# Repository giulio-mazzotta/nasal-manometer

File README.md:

# nasal-manometer

This repository contains the circuit design and the software to measure the nasal pressure while speaking using a nasal cannula.

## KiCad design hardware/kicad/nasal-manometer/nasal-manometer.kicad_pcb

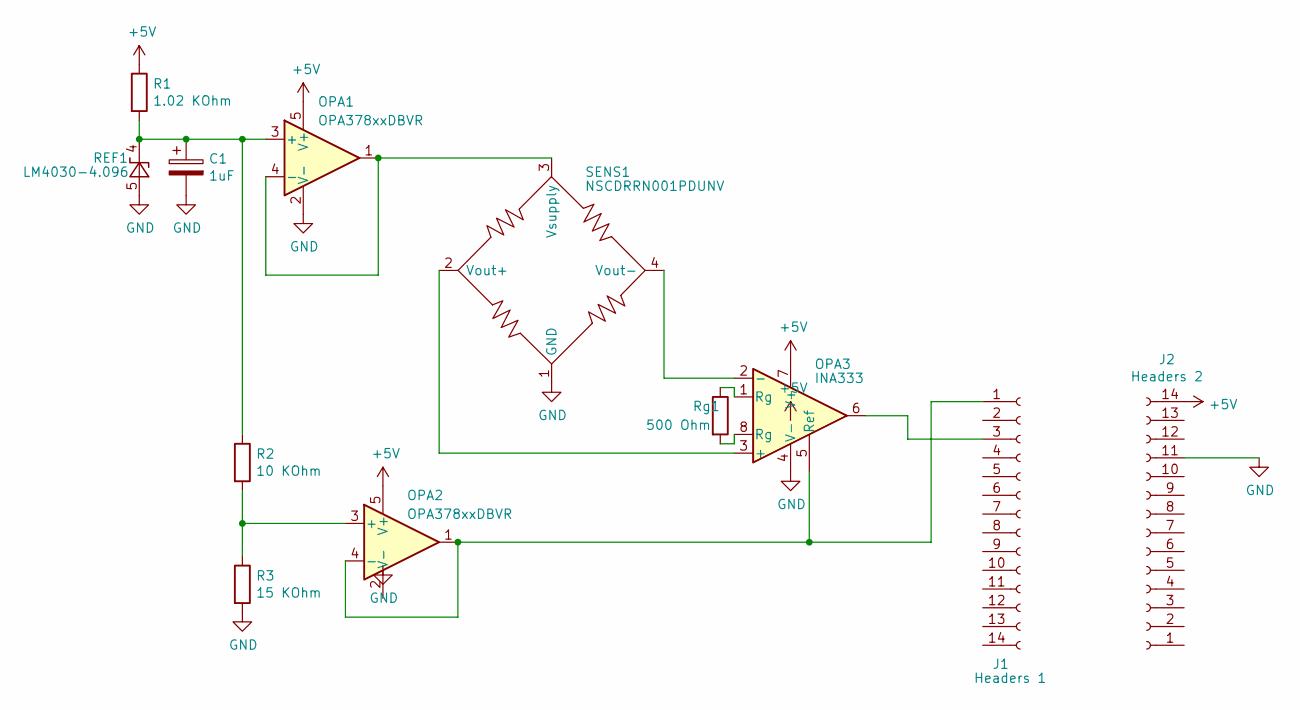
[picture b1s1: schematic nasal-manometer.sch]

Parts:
C1: 1uF; CP_EIA-2012-15_AVX-P
J1: Headers 1; PinSocket_1x14_P2.54mm_Vertical
J2: Headers 2; PinSocket_1x14_P2.54mm_Vertical
OPA1, OPA2: OPA378xxDBVR; SOT-23-5
OPA3: INA333; VSSOP-8_3.0x3.0mm_P0.65mm
R1: 1.02 KOhm; R_0603_1608Metric
R2: 10 KOhm; R_0805_2012Metric
R3: 15 KOhm; R_0805_2012Metric
REF1: LM4030-4.096; SOT-23-5
Rg1: 500 Ohm; R_0603_1608Metric
SENS1: NSCDRRN001PDUNV; DIP-8_RR

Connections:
+5V: J2.14, OPA1.5 (V+), OPA2.5 (V+), OPA3.7 (V+), R1.1
GND: C1.2, J2.11, OPA1.2 (V-), OPA3.4 (V-), R3.2, REF1.5 (A), SENS1.1 (GND)
unnamed: C1.1, OPA1.3 (+), R1.2, R2.1, REF1.4 (K)
unnamed: J1.1, OPA2.1, OPA2.4 (-), OPA3.5 (Ref)
unnamed: J1.3, OPA3.6
unnamed: OPA1.1, OPA1.4 (-), SENS1.3 (Vsupply)
unnamed: OPA2.3 (+), R2.2, R3.1
unnamed: OPA3.1 (Rg), Rg1.1
unnamed: OPA3.2 (-), SENS1.4 (Vout-)
unnamed: OPA3.3 (+), SENS1.2 (Vout+)
unnamed: OPA3.8 (Rg), Rg1.2

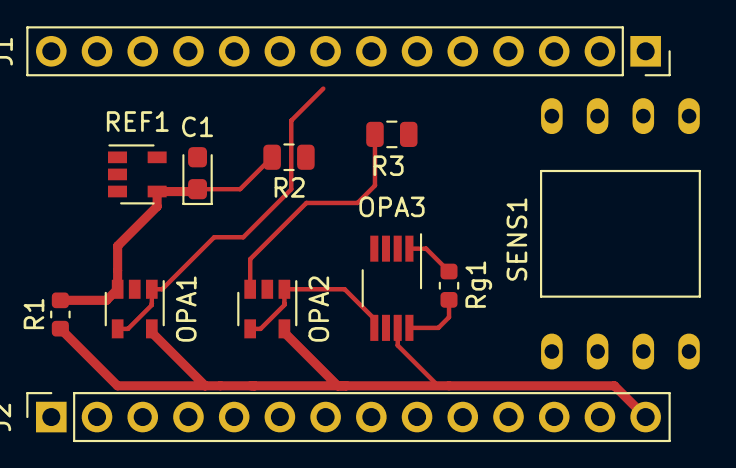
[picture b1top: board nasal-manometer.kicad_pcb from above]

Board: 2 copper layers, 12 parts (0 on the bottom side), 11 nets.

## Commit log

2019-05-05 Update README.md
    Added a brief description of the project
2019-05-05 Structuring folders and adding components list
2019-05-05 Started kicad project and updated components list
2019-05-07 Switched to Arduino MKR and updated ref voltage
2019-05-07 Change voltage reference chip
2019-05-08 Adding buffer OPA
2019-05-08 Added capacitors in compontentslist to stabilise ref voltage
2019-05-08 added passive components to list
2019-05-08 Updating .gitignore to ignore useless kicad files
2019-05-08 deleting sym-lib-table
2019-05-08 Fixed csv table
2019-05-08 Started schematic
2019-05-08 tidying up component libraries
2019-05-09 Progress on the schematic
2019-05-09 Added reference to components
2019-05-09 Schematic updated
2019-05-09 Building the board
